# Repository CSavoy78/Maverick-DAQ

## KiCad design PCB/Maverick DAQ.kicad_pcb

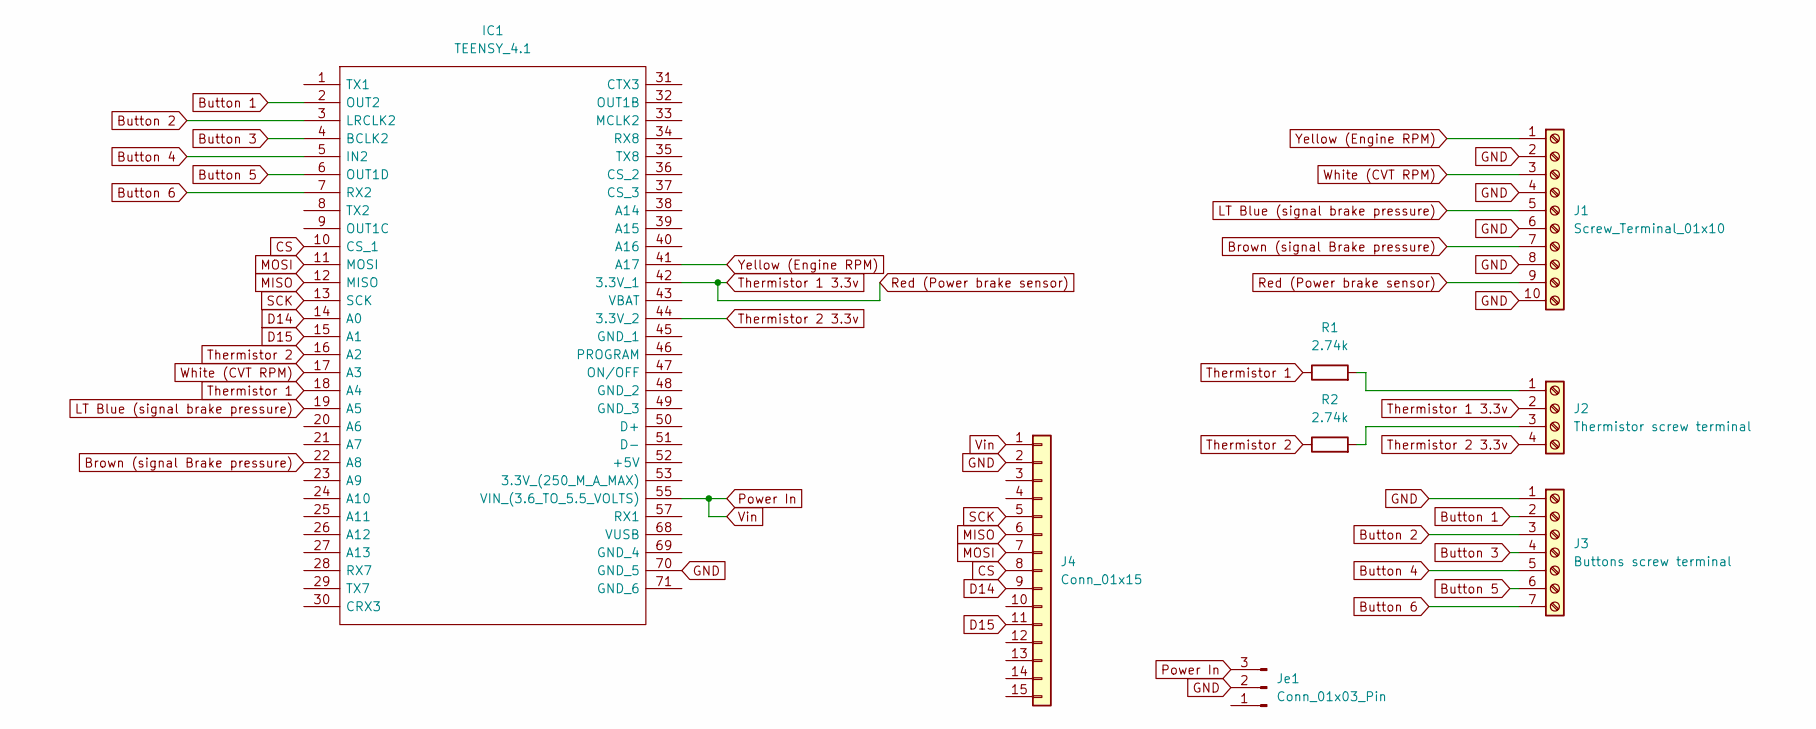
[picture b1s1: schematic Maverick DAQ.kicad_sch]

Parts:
IC1: TEENSY_4.1; TEENSY41; Manufacturer_Part_Number TEENSY 4.1
J1: Screw_Terminal_01x10; PinHeader_1x10_P2.54mm_Vertical
J2: Thermistor screw terminal; PinSocket_1x04_P2.54mm_Vertical
J3: Buttons screw terminal; PinSocket_1x07_P2.54mm_Vertical
J4: Conn_01x15; PinSocket_1x15_P2.54mm_Vertical
Je1: Conn_01x03_Pin; PinHeader_1x03_P2.54mm_Vertical
R1, R2: 2.74k; R_0402_1005Metric_Pad0.72x0.64mm_HandSolder

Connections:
Brown (signal Brake pressure): IC1.22 (A8), J1.7
Button 1: IC1.2 (OUT2), J3.2
Button 2: IC1.3 (LRCLK2), J3.3
Button 3: IC1.4 (BCLK2), J3.4
Button 4: IC1.5 (IN2), J3.5
Button 5: IC1.6 (OUT1D), J3.6
Button 6: IC1.7 (RX2), J3.7
CS: IC1.10 (CS_1), J4.8
D14: IC1.14 (A0), J4.9
D15: IC1.15 (A1), J4.11
GND: IC1.70 (GND_5), J1.2, J1.4, J1.6, J1.8, J1.10, J3.1, J4.2, Je1.2
LT Blue (signal brake pressure): IC1.19 (A5), J1.5
MISO: IC1.12 (MISO), J4.6
MOSI: IC1.11 (MOSI), J4.7
unnamed: J2.1, R1.2
unnamed: J2.3, R2.2
Power In: IC1.55 (VIN_(3.6_TO_5.5_VOLTS)), J4.1, Je1.3
Red (Power brake sensor): IC1.42 (3.3V_1), J1.9, J2.2
SCK: IC1.13 (SCK), J4.5
Thermistor 1: IC1.18 (A4), R1.1
Thermistor 2: IC1.16 (A2), R2.1
Thermistor 2 3.3v: IC1.44 (3.3V_2), J2.4
White (CVT RPM): IC1.17 (A3), J1.3
Yellow (Engine RPM): IC1.41 (A17), J1.1

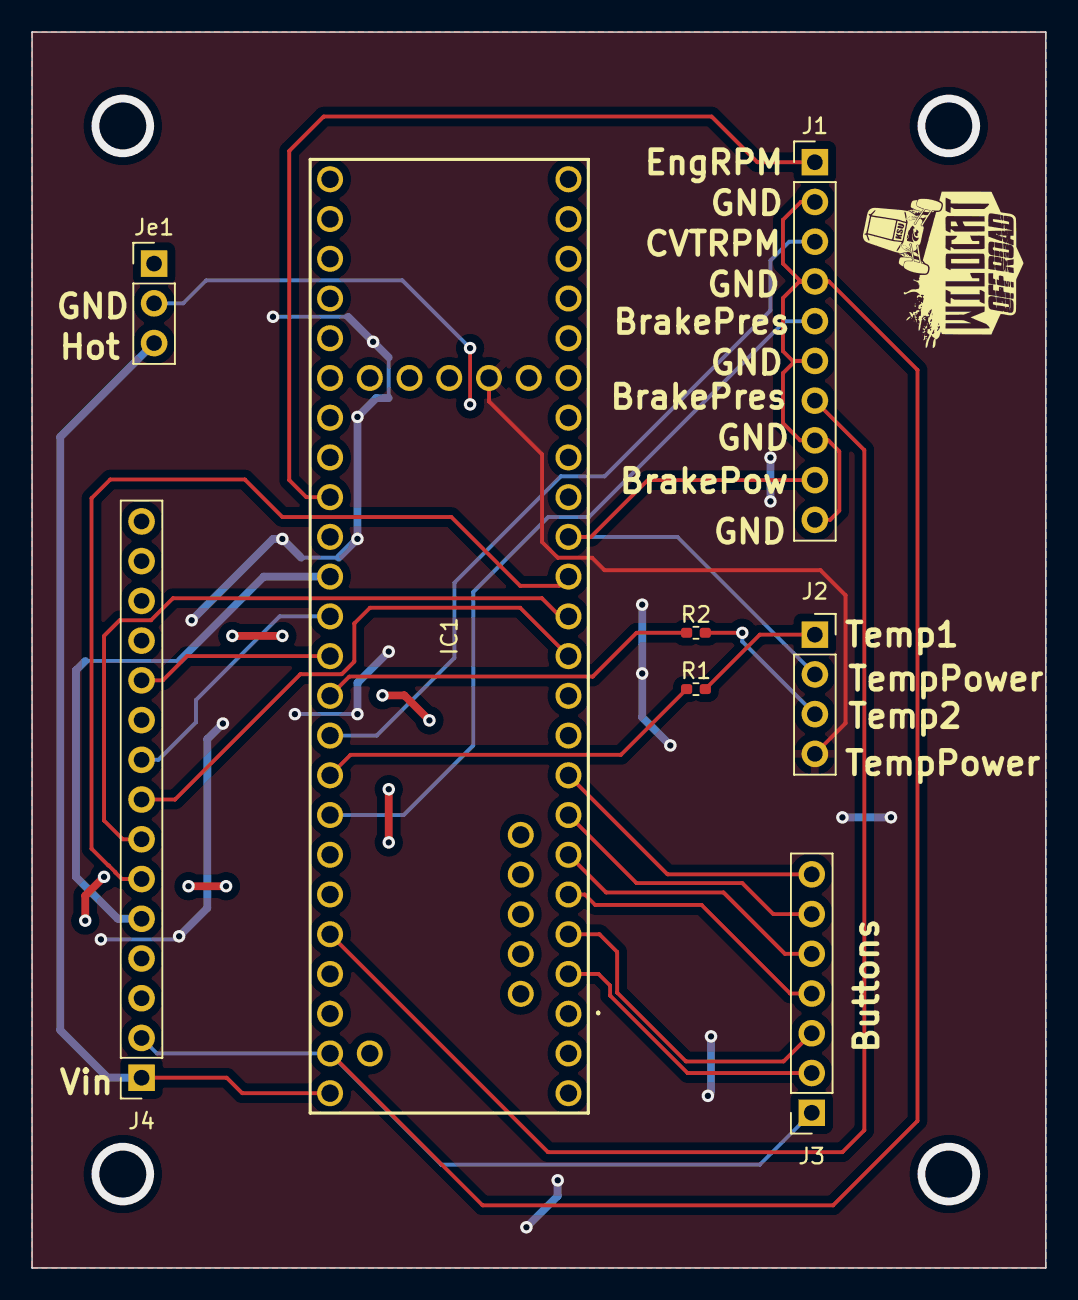
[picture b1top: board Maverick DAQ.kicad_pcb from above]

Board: 2 copper layers, 64.8 x 79.0 mm, 8 parts (0 on the bottom side), 24 nets.

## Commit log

2025-04-01 Add files via upload
    New PCB design
2025-04-01 .gitkeep
2025-04-01 Delete PCB/git.keep
    useless file
2025-04-01 Delete Maverick DAQ.kicad_sch
    Moved to PCB
2025-04-01 Delete Maverick DAQ.kicad_pro
    Moved to PCB
2025-04-01 Delete Maverick DAQ.kicad_pcb
    Moved to PCB
2025-04-01 Create keep
2025-04-01 Add files via upload
    Code for Maverick Teensy
2025-04-01 Add files via upload
    Properly named code
2025-04-01 Delete Arduino Code/MAV DAQ Arduino.ino
    bad name, new file uploaded
2025-04-01 Delete Arduino Code/keep
    useless file
2025-04-01 Delete Shcematics_in_sheets directory
    typo lol
2025-04-01 Additional Excel File
2025-04-01 Delete Additional Files/keep
    Useless
